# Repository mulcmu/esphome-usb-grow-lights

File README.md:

# esphome-usb-grow-lights
Custom PCB to drive usb powered grow lights via ESP8266 and ESPHome.

Project logs posted at https://hackaday.io/project/186050-iot-the-usb-grow-lights.

led_timer_demo.ino simple Arduino sketch to test circuit operation.

basic config.yaml ESPhome is configuration file for control the lights via home assistant and binary sensors for the button states.

Rev2 of the PCB has been tested.  Do not populate the voltage supervisor or get one with a 2.7V threshold level.

The 5V LED bulb drew 900mA at 5V.  Testing a stock control board shows the PWM frequency was 60 Hz with max duty cycle of 15%.  This limits the current from the power supply and doesn't drive the LEDs too hard to prolong lifespan.

TODO:

- ~~Update Rev 2 BOM and post.~~  3.1V supervisor and 2A fuse
- ~~Add ESPHome logic for local control at the light~~
- Design compatible 3d printed case for other generic usb lights

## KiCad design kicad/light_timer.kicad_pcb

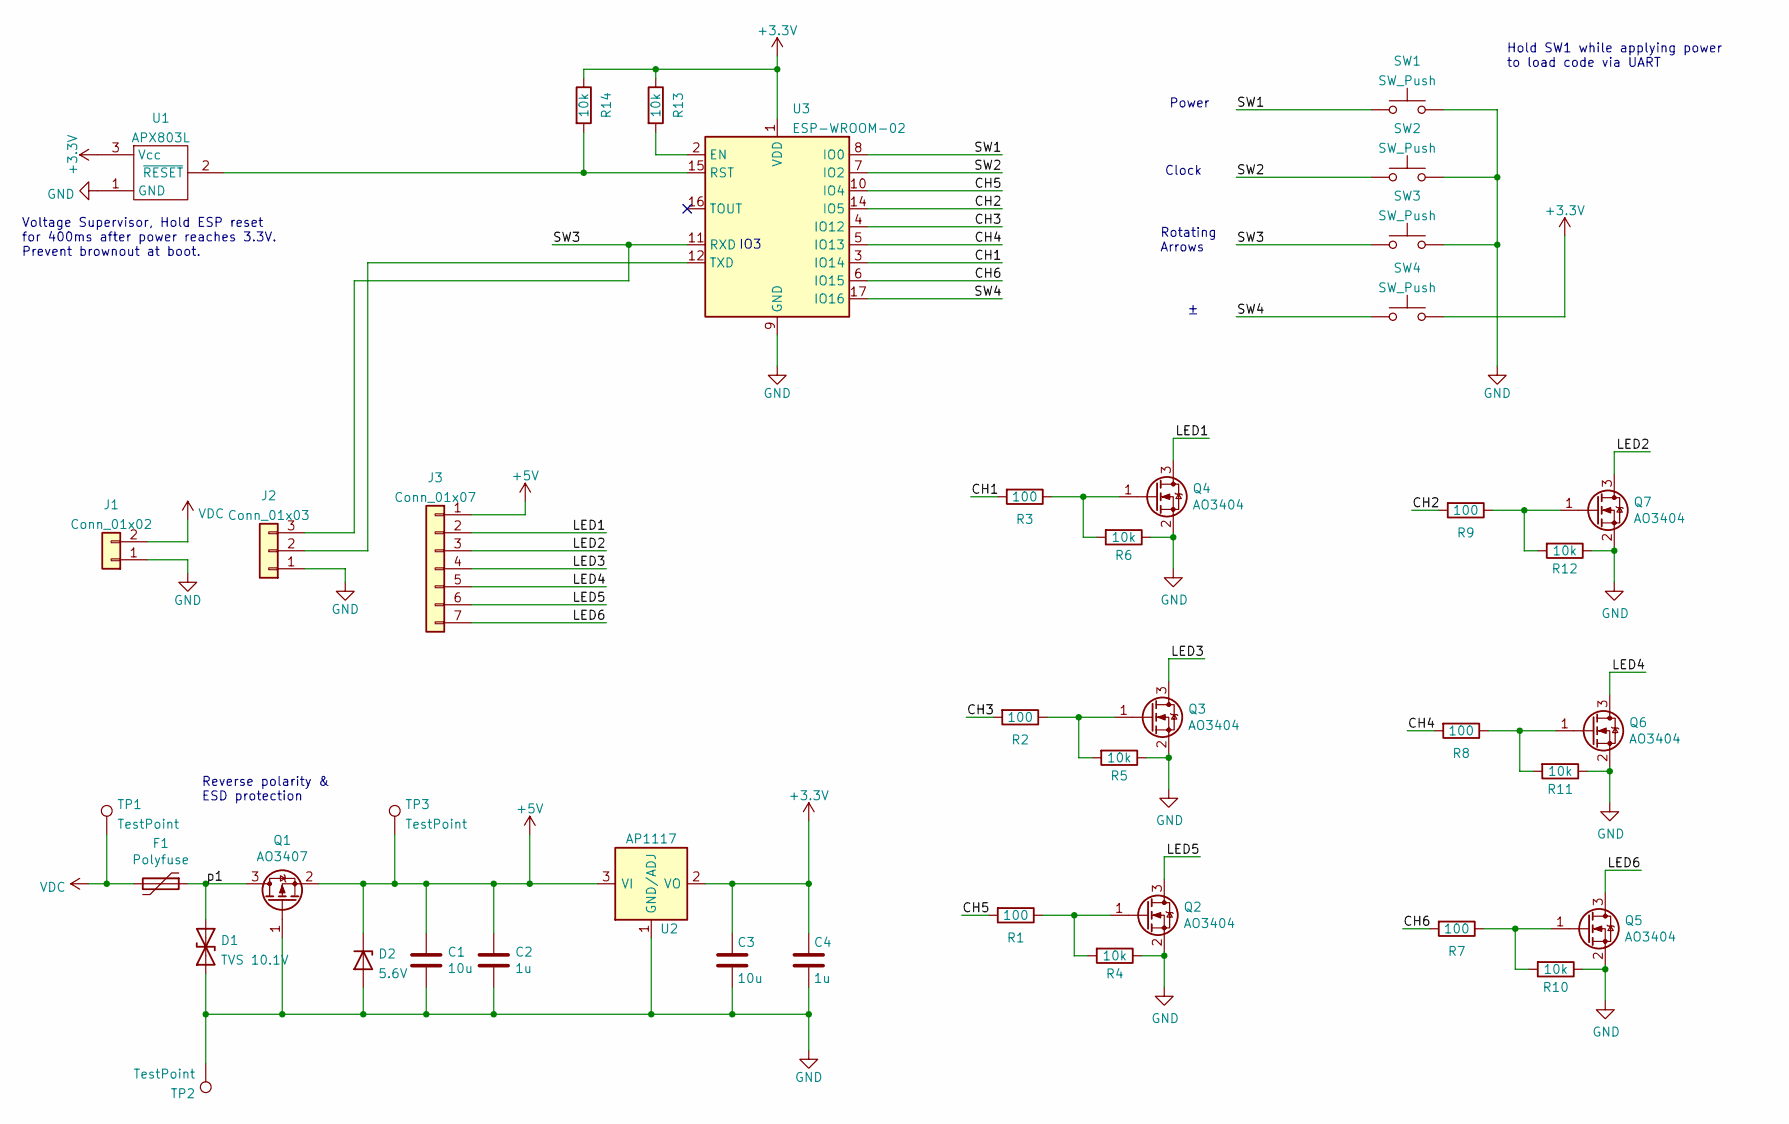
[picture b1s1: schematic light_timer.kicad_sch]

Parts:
C1, C3: 10u; C_0805_2012Metric
C2, C4: 1u; C_0805_2012Metric
D1: TVS 10.1V; D_SMB
D2: 5.6V; D_SOD-123
F1: Polyfuse; R_1210_3225Metric_Pad1.30x2.65mm_HandSolder
J1: Conn_01x02; PinHeader_1x02_P2.54mm_Vertical
J2: Conn_01x03; PinHeader_1x03_P2.54mm_Vertical
J3: Conn_01x07; PinHeader_1x07_P2.00mm_Vertical
Q1: AO3407; SOT-23
Q2, Q3, Q4, Q5, Q6, Q7: AO3404; SOT-23
R1, R2, R3, R7, R8, R9: 100; R_0805_2012Metric
R4, R5, R6, R10, R11, R12, R13, R14: 10k; R_0805_2012Metric
SW1, SW2, SW3, SW4: SW_Push; 5.2mm button
TP1, TP2, TP3: TestPoint; TestPoint_THTPad_D2.5mm_Drill1.2mm
U1: APX803L; SOT-23
U2: AP1117; SOT-223
U3: ESP-WROOM-02

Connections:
+3V3: C3.1, C4.1, R13.1, R14.1, SW4.2, U1.3 (Vcc), U2.2 (VO), U2.4 (VO), U3.1 (VDD)
+5V: C1.1, C2.1, D2.1 (K), J3.1, Q1.2 (S), TP3.1, U2.3 (VI)
/CH1: R3.2, U3.3 (IO14)
/CH2: R9.2, U3.14 (IO5)
/CH3: R2.2, U3.4 (IO12)
/CH4: R8.2, U3.5 (IO13)
/CH5: R1.2, U3.10 (IO4)
/CH6: R7.2, U3.6 (IO15)
/LED1: J3.2, Q4.3 (D)
/LED2: J3.3, Q7.3 (D)
/LED3: J3.4, Q3.3 (D)
/LED4: J3.5, Q6.3 (D)
/LED5: J3.6, Q2.3 (D)
/LED6: J3.7, Q5.3 (D)
/SW1: SW1.1, U3.8 (IO0)
/SW2: SW2.1, U3.7 (IO2)
/SW3: J2.3, SW3.1, U3.11 (RXD)
/SW4: SW4.1, U3.17 (IO16)
/p1: D1.2 (A2), F1.1, Q1.3 (D)
GND: C1.2, C2.2, C3.2, C4.2, D1.1 (A1), D2.2 (A), J1.1, J2.1, Q1.1 (G), Q2.2 (S), Q3.2 (S), Q4.2 (S), Q5.2 (S), Q6.2 (S), Q7.2 (S), R4.1, R5.1, R6.1, R10.1, R11.1, R12.1, SW1.2, SW2.2, SW3.2, TP2.1, U1.1 (GND), U2.1 (GND/ADJ), U3.9 (GND), U3.13 (GND), U3.18 (GND), U3.19 (GND)
unnamed: J2.2, U3.12 (TXD)
unnamed: Q2.1 (G), R1.1, R4.2
unnamed: Q3.1 (G), R2.1, R5.2
unnamed: Q4.1 (G), R3.1, R6.2
unnamed: Q5.1 (G), R7.1, R10.2
unnamed: Q6.1 (G), R8.1, R11.2
unnamed: Q7.1 (G), R9.1, R12.2
unnamed: R13.2, U3.2 (EN)
unnamed: R14.2, U1.2 (~RESET), U3.15 (RST)
VDC: F1.2, J1.2, TP1.1

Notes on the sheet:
Clock
Reverse polarity & ESD protection
Rotating Arrows
Hold SW1 while applying power to load code via UART
Power
IO3
Voltage Supervisor, Hold ESP reset for 400ms after power reaches 3.3V. Prevent brownout at boot.

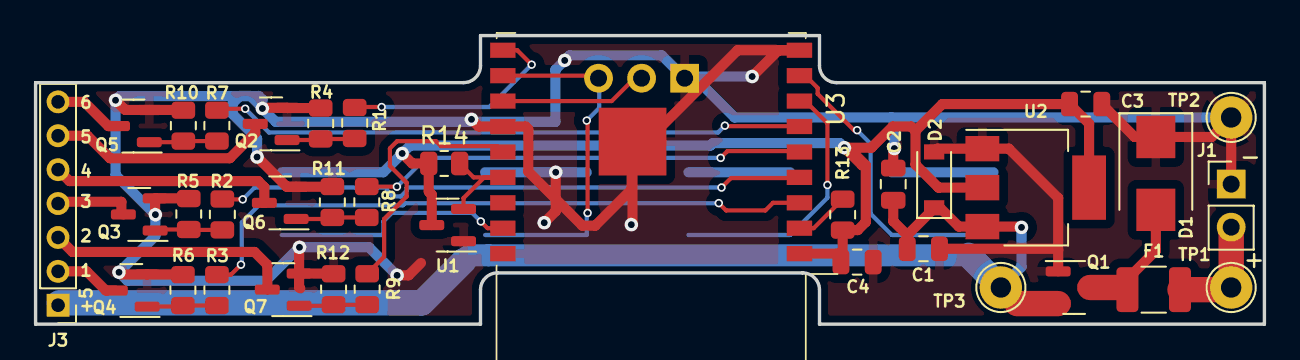
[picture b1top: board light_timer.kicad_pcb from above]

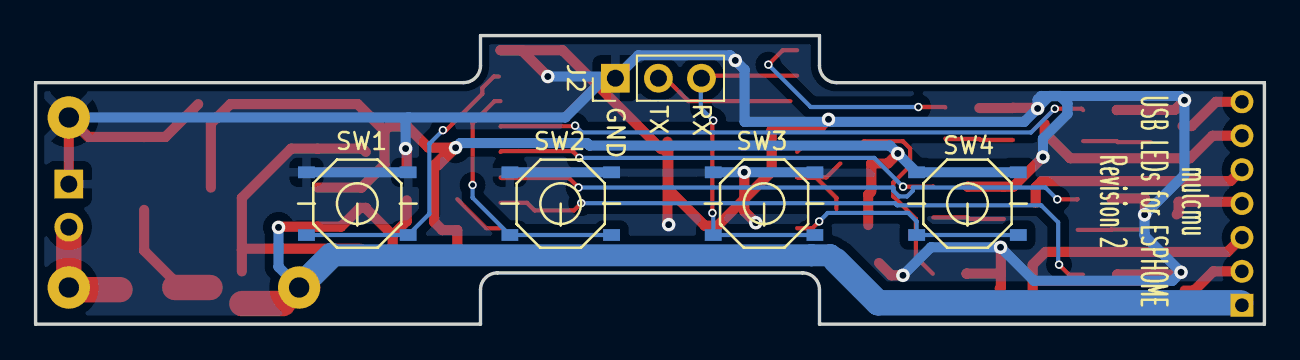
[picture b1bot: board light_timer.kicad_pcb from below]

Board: 2 copper layers, 72.5 x 17.0 mm, 41 parts (5 on the bottom side), 30 nets.

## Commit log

2022-06-28 PCB Rev 2
2022-07-01 add test code
2026-05-23 kicad upload
